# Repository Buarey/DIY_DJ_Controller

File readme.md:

# DIY DJ Controller

Homemade CDJ-style DJ controller with a 3D-printed enclosure, hand-built electronics, and custom firmware.

This repository documents:
- the current stable Mixxx prototype
- the firmware and Mixxx mapping that make it work
- the next hardware direction for a cleaner v2 build
- open-source hardware, firmware, and documentation for builders who want to contribute

<table>
  <tr>
    <td></td>
    <td></td>
  </tr>
  <tr>
    <td></td>
    <td></td>
  </tr>
</table>

## Status

- `v1` is the stable Mixxx-focused version
- the controller has been built, flashed, and used successfully as a working prototype
- Rekordbox was tested, but the jog wheels never became usable enough for a real workflow
- because of that, Rekordbox is not a supported target for this hardware revision

## Current Version

- `MCU`: SparkFun Pro Micro / ATmega32U4
- `Firmware`: PlatformIO + Arduino + `MIDIUSB`
- `Inputs`: `PCF8575` for buttons, `74HC4067` for analog controls, 3 rotary encoders
- `Mechanical`: custom 3D-printed enclosure designed in Fusion 360
- `Software target`: Mixxx

The current prototype includes:
- two-deck transport and loop control
- EQ, filter, gain, volume, tempo, and crossfader control
- jog wheels
- music browsing and load controls

## V1 Hardware Summary

- `MCU`: SparkFun Pro Micro / ATmega32U4
- `Button expander`: `PCF8575` for 16 buttons
- `Analog mux`: `74HC4067` for 15 potentiometers
- `Encoders`: 3 total
  - 1 browse encoder
  - 2 jog wheel encoders
- `Encoder model`: Alps `EC11E` vertical rotary encoder, `H20mm`
- `Button model`: Omron `B3F-40xx`, 12x12 mm THT tactile switch
- `Direct buttons on MCU`: `A1`, `A2`, `A3`
- `Potentiometers`: 15 total
  - `Linear model`: `B103` 75 mm linear slide potentiometer, 10 kOhm
  - `Rotary model`: TT Electronics `P0915N` vertical rotary potentiometer

## V1 Materials List

This is the practical parts list for rebuilding the current working v1 prototype.

| Qty | Material | Notes |
| --- | --- | --- |
| 1 | SparkFun Pro Micro / ATmega32U4 board | The KiCad v1 schematic uses a USB-C Pro Micro clone footprint. Use the matching USB cable for the board you build with. |
| 1 | `PCF8575` / HW-331 16-bit I2C IO expander module | Handles the 16 deck buttons. |
| 1 | `CD74HC4067` / `74HC4067` 16-channel analog multiplexer module | Handles the 15 analog controls. |
| 18 | Omron `B3F-40xx` 12x12 mm THT tactile switches | 16 deck buttons plus 2 direct music-selection buttons. |
| 3 | Alps `EC11E` vertical rotary encoders, `H20mm` | 1 browse encoder plus 2 jog wheel encoders. |
| 10 | TT Electronics `P0915N` vertical rotary potentiometers | Gain, EQ, filter, and other rotary controls. |
| 5 | `B103` 75 mm linear slide potentiometers, 10 kOhm | Deck volume, tempo, and crossfader controls. |
| 1 | 3D-printed enclosure body | `3D models/DIY_CDJ_body.stl`. |
| 1 | 3D-printed enclosure lid | `3D models/DIY_CDJ_lid.stl`. |
| 1 each | 3D-printed caps and control parts | `crossfader.stl`, `cue.stl`, `encoder.stl`, `joggingWheel.stl`, `knob.stl`, `performance-pad.stl`, and `play-pause.stl`. |
| As needed | Hookup wire, solder, and 2.54 mm headers | The stable v1 prototype is hand-wired, not PCB-based. |

The firmware currently defines 3 direct music-selection inputs on `A1`, `A2`, and `A3`, but the KiCad v1 schematic places 18 tactile switches total. Add one extra switch if you wire all 3 direct inputs. The schematic also contains 16 resistor placeholders with no values or footprints assigned yet, so treat those as schematic TODOs rather than an order-ready BOM line.

## V1 Wiring Summary

These are the important firmware-defined connections for the current working Mixxx version.

### Wiring Diagrams

### I2C / Button Expander

- `SDA` -> pin `2`
- `SCL` -> pin `3`
- `PCF8575` address is auto-detected on boot in the `0x20` to `0x27` range

### 74HC4067 Multiplexer

- `MUX signal` -> `A0`
- `S0` -> pin `15`
- `S1` -> pin `14`
- `S2` -> pin `16`
- `S3` -> pin `10`

### Rotary Encoders

- `Browse encoder` -> pins `4` and `5`
- `Jog wheel 1` -> pins `8` and `9`
- `Jog wheel 2` -> pins `6` and `7`

### Direct Buttons

- `A3` -> note `76`
- `A2` -> note `77`
- `A1` -> note `78`

## V1 Current Input Map

### PCF8575 Buttons

- `Button 0` -> Deck 1 Loop Out
- `Button 1` -> Deck 1 Loop In
- `Button 2` -> Deck 1 Hotcue 3
- `Button 3` -> Deck 1 Hotcue 4
- `Button 4` -> Deck 1 Hotcue 1
- `Button 5` -> Deck 1 Hotcue 2
- `Button 6` -> Deck 1 Cue
- `Button 7` -> Deck 1 Play/Pause
- `Button 8` -> Deck 2 Hotcue 4
- `Button 9` -> Deck 2 Hotcue 3
- `Button 10` -> Deck 2 Hotcue 1
- `Button 11` -> Deck 2 Hotcue 2
- `Button 12` -> Deck 2 Cue
- `Button 13` -> Deck 2 Play/Pause
- `Button 14` -> Deck 2 Loop In
- `Button 15` -> Deck 2 Loop Out

### Potentiometers

- `Pot 0 / CC 10` -> Deck 1 Gain
- `Pot 1 / CC 11` -> Deck 2 Gain
- `Pot 2 / CC 12` -> Deck 1 High EQ
- `Pot 3 / CC 13` -> Deck 2 High EQ
- `Pot 4 / CC 14` -> Deck 1 Mid EQ
- `Pot 5 / CC 15` -> Deck 2 Mid EQ
- `Pot 6 / CC 16` -> Deck 1 Low EQ
- `Pot 7 / CC 17` -> Deck 2 Low EQ
- `Pot 8 / CC 18` -> Deck 1 Filter
- `Pot 9 / CC 19` -> Deck 2 Filter
- `Pot 10 / CC 20` -> Deck 2 Volume
- `Pot 11 / CC 21` -> Deck 2 Tempo
- `Pot 12 / CC 22` -> Deck 1 Volume
- `Pot 13 / CC 23` -> Crossfader
- `Pot 14 / CC 24` -> Deck 1 Tempo

### Browser And Jog Controls

- `Browse encoder / CC 25` -> library scroll
- `A1 / note 78` -> Load selected track to Deck 1
- `A2 / note 77` -> Load selected track to Deck 2
- `A3 / note 76` -> Enter or expand selected folder
- `Jog wheel on pins 8/9 / CC 26` -> currently mapped to Deck 2
- `Jog wheel on pins 6/7 / CC 27` -> currently mapped to Deck 1

## V1 Firmware

The current firmware lives in `CDJ_firmware/src/main.cpp`.

### Current Behavior

- auto-detects the `PCF8575` on boot
- configures the expander pins as input pull-high
- reads 16 buttons through the `PCF8575`
- reads 15 analog controls through the `74HC4067`
- reads 3 rotary encoders
- reads direct top buttons on `A1`, `A2`, and `A3`
- sends MIDI note and CC messages through `MIDIUSB`
- uses an additional filter on the browse encoder to reduce event spam in Mixxx

### Build Target

`CDJ_firmware/platformio.ini` currently targets:

```ini
[env:sparkfun_promicro16]
platform = atmelavr
board = sparkfun_promicro16
framework = arduino
lib_deps =
  arduino-libraries/MIDIUSB @ ^1.0.5
```

## Repo Layout

- `CDJ_firmware/` - firmware source and PlatformIO config
- `controllers/mixx_Mapping/` - Mixxx XML and JS mapping
- `controllers/rekordbox/` - Rekordbox mapping reference and notes
- `pics/` - renders and prototype photos
- `reference circuits/` - circuit reference images
- `PCB/` - KiCad schematic, PCB, and custom symbols/footprints
- `3D models/` - printable parts and Fusion 360 source archive
- `CONTRIBUTING.md` - contribution guide
- `.github/` - issue templates, pull request template, and CI workflow

## Source Of Truth

- `Firmware`: `CDJ_firmware/src/main.cpp`
- `Mixxx XML mapping`: `controllers/mixx_Mapping/DJC-DIY.midi.xml`
- `Mixxx JS mapping`: `controllers/mixx_Mapping/DJC-DIY-scripts.js`

For exact control behavior, use those files instead of this README.

## Contributing

Contributions are welcome. The most useful contributions right now are practical build reports, Mixxx mapping fixes, firmware cleanup, PCB review, parts substitutions, enclosure fit notes, and documentation improvements.

Before starting a large hardware or firmware change, open an issue so the direction can be discussed. Small documentation fixes can go straight to a pull request.

Useful starter work:

- test the current Mixxx mapping on another OS or Mixxx version
- document compatible Pro Micro clones, encoders, buttons, and potentiometers
- improve wiring photos or assembly notes
- review the KiCad v1 schematic and PCB TODOs
- add real build notes for 3D-print settings and fit adjustments

See `CONTRIBUTING.md` for the full workflow and pull request checklist.

## Getting Started

### Firmware

1. Install [PlatformIO](https://platformio.org/) in VS Code.
2. Open `CDJ_firmware/`.
3. Connect the SparkFun Pro Micro by USB.
4. Build or upload:

```bash
pio run
pio run --target upload
```

### Mixxx

Copy these files into your Mixxx controller mapping folder:

- `controllers/mixx_Mapping/DJC-DIY.midi.xml`
- `controllers/mixx_Mapping/DJC-DIY-scripts.js`

Then enable the mapping in Mixxx.

## Important Notes

- The stable path for this project is Mixxx, not Rekordbox.
- The prototype is still hand-wired and not PCB-based yet.
- The current jog wheel assignment is swapped between physical control and deck mapping.
- Rekordbox support should be treated as future hardware research, not a feature of this version.

## V2 Plan

V2 is a hardware redesign focused on one goal: keep a single `USB-C` cable to the computer and add a built-in `3.5 mm` headphone cue output.

- `Master` stays on the computer side
- the controller provides only `Headphones / Cue`
- the project stays Mixxx-first

### Electronics Plan

- `Prototype MCU`: `SparkFun Thing Plus ESP32-S3`
- `Custom PCB MCU`: `ESP32-S3-WROOM-1`
- `Headphone audio`: `Adafruit TLV320DAC3100` or equivalent small I2S headphone DAC/codec
- `External ports`: one `USB-C`, one `3.5 mm TRS` headphone jack
- `Existing controls to keep initially`: `PCF8575`, `74HC4067`, jog encoders, browse encoder, buttons, and potentiometers

### Core Connections

- `USB-C` -> `ESP32-S3`
- `ESP32-S3 I2S` -> `TLV320DAC3100` audio data
- `ESP32-S3 I2C` -> `TLV320DAC3100` configuration
- `TLV320DAC3100` -> `3.5 mm TRS` headphone jack
- `ESP32-S3` -> existing control hardware

### Firmware Work

- port the controller logic from `ATmega32U4` to `ESP32-S3`
- expose one composite USB device with `MIDI + audio`
- keep the current control behavior as close to `v1` as possible
- send Mixxx cue audio to the headphone DAC

### Rekordbox Note

`ESP32-S3` is a much better platform for future USB experiments, but it does not guarantee Rekordbox compatibility or working jog wheels. V2 should still be treated as a Mixxx-first design.

## License

This project uses separate licenses by file type:

| Files | License |
| --- | --- |
| Firmware and controller mappings | GNU General Public License v3.0 only (`GPL-3.0-only`) |
| PCB, wiring, CAD, and 3D hardware design files | CERN Open Hardware Licence Version 2 - Strongly Reciprocal (`CERN-OHL-S-2.0`) |
| Documentation, photos, videos, and other media | Creative Commons Attribution 4.0 International (`CC-BY-4.0`) |

See `LICENSE.md`, `LICENSE-SOFTWARE.txt`, `LICENSE-HARDWARE.txt`, and `LICENSE-DOCS.txt` for details.

This project was inspired by my friend [@mandiclab](https://github.com/mandiclab) and the [djc-diy](https://github.com/mandiclab/djc-diy) project.

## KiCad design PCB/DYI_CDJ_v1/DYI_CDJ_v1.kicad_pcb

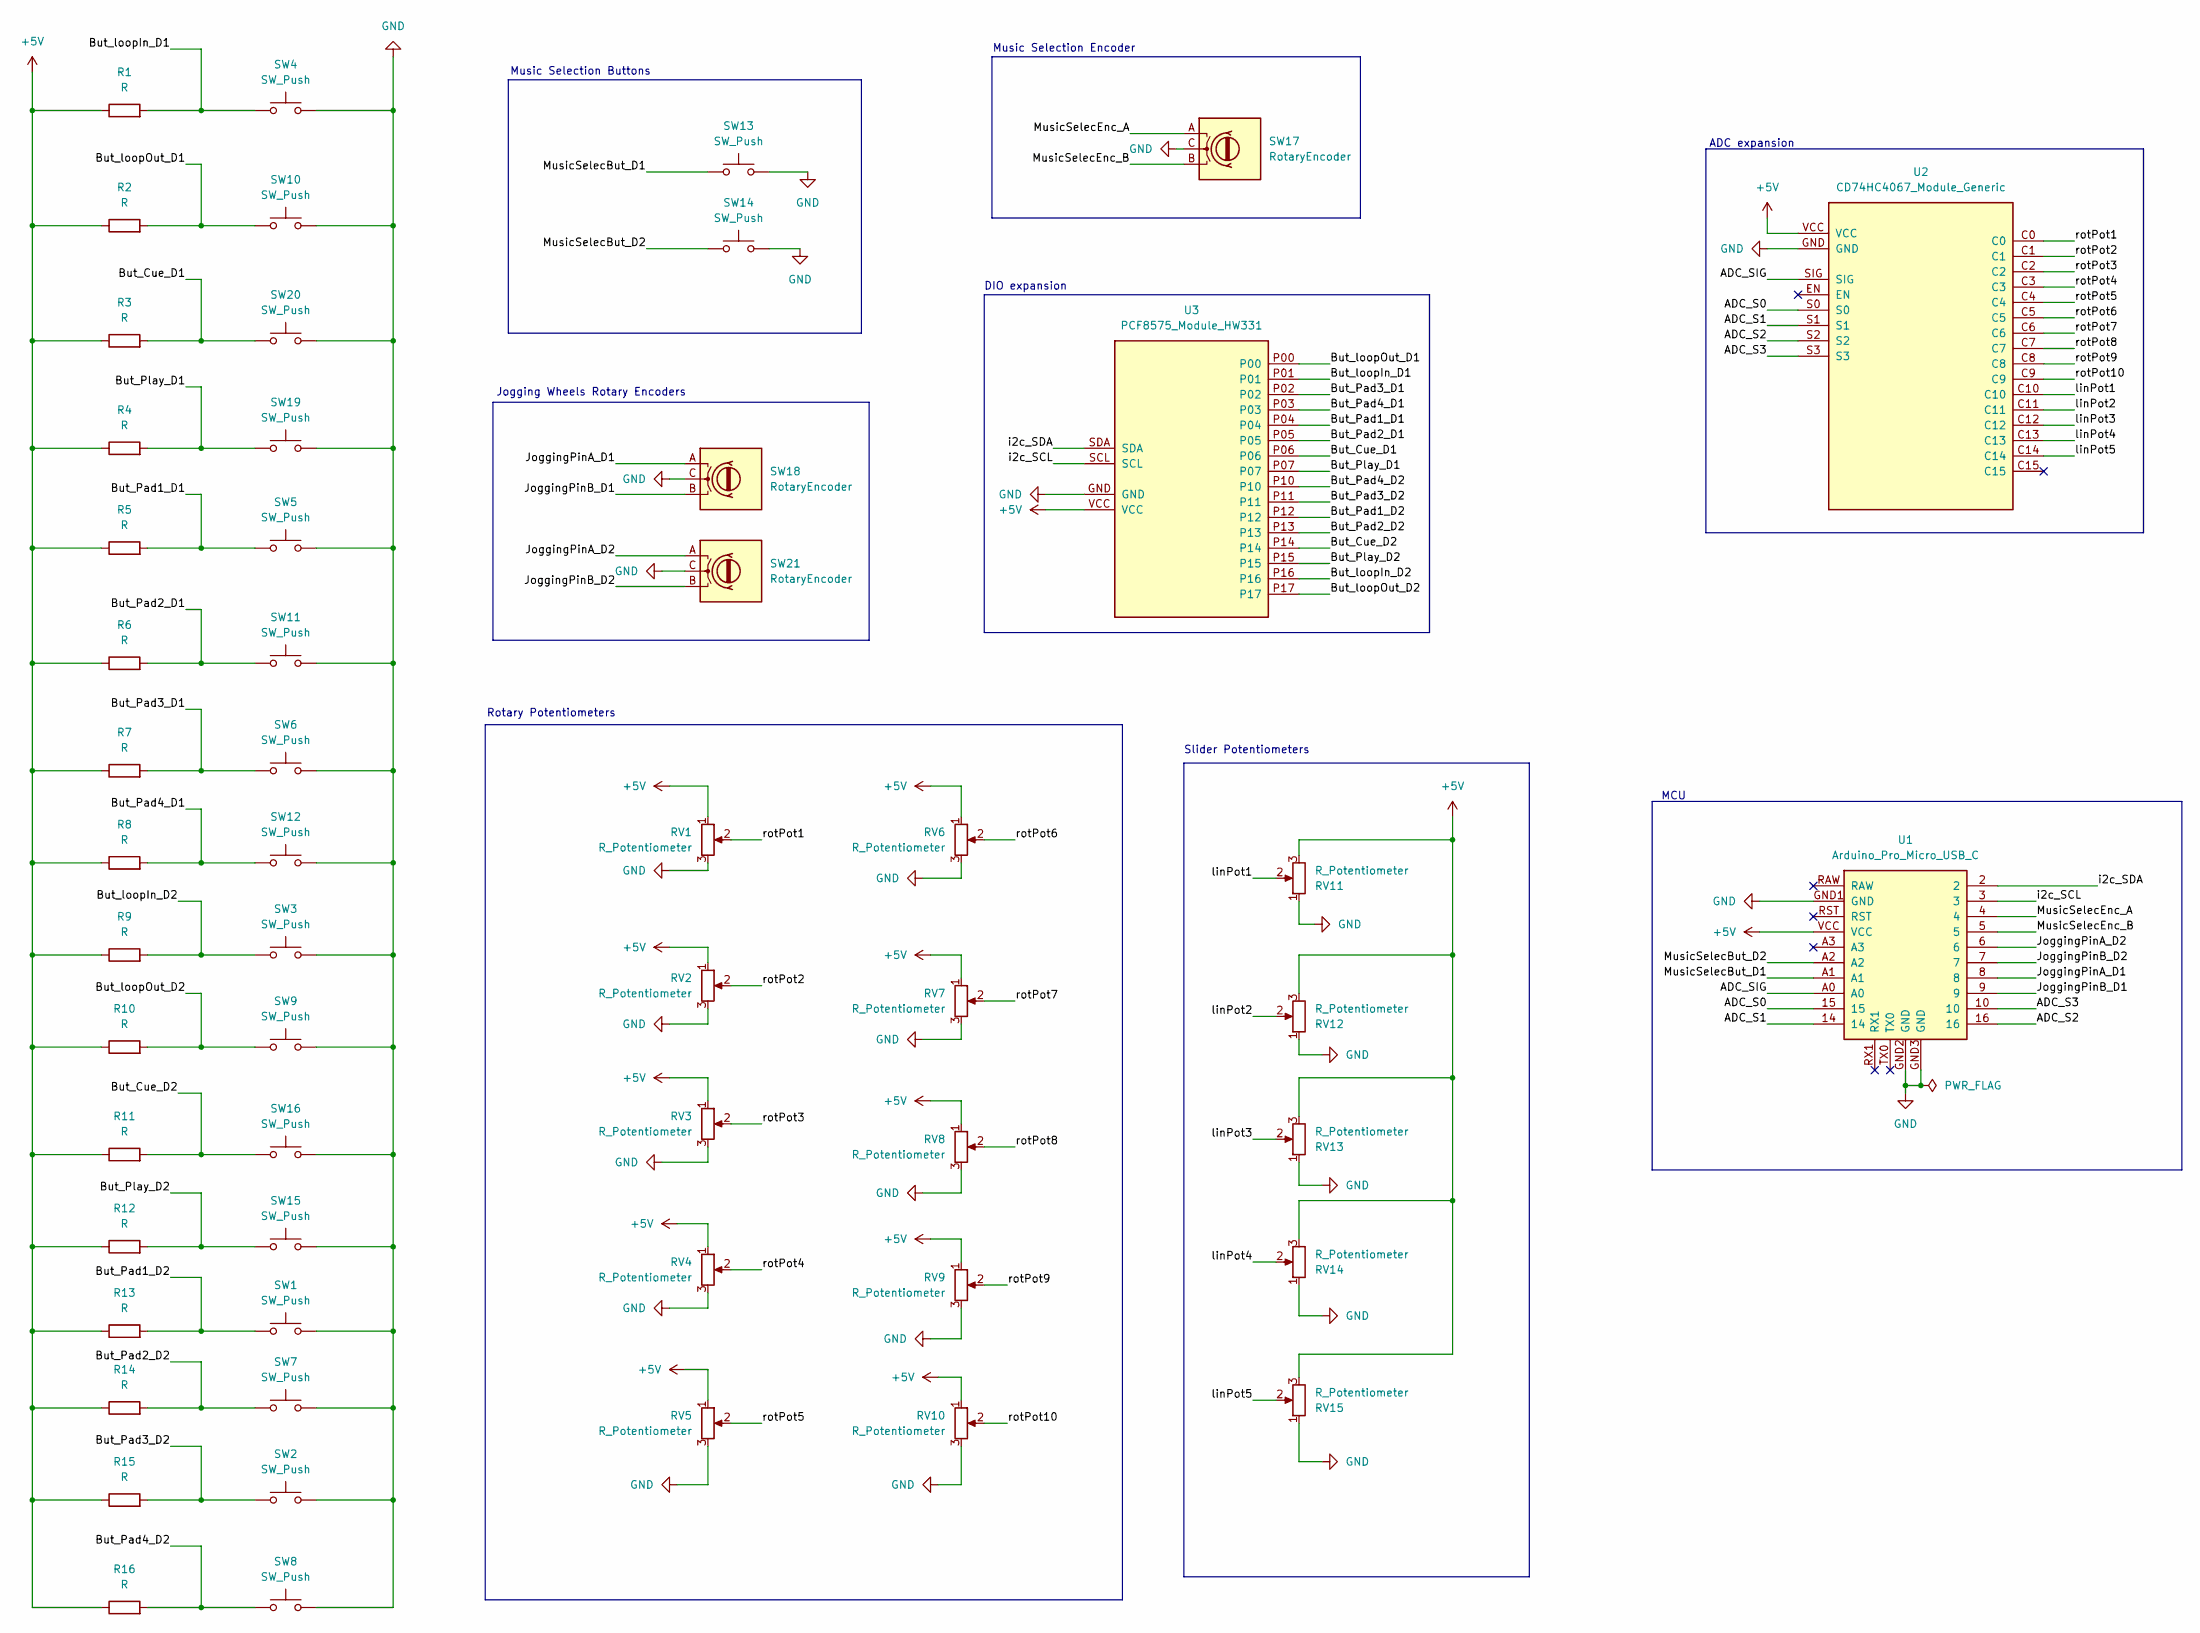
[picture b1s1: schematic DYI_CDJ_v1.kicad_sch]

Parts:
R1, R2, R3, R4, R5, R6, R7, R8, R9, R10, R11, R12, R13, R14, R15, R16: R; R_Axial_DIN0207_L6.3mm_D2.5mm_P10.16mm_Horizontal
RV1, RV2, RV3, RV4, RV5, RV6, RV7, RV8, RV9, RV10: R_Potentiometer; Potentiometer_TT_P0915N
RV11, RV12, RV13, RV14, RV15: R_Potentiometer; Potentiometer_Bourns_PTA6043_Single_Slide
SW1, SW2, SW3, SW4, SW5, SW6, SW7, SW8, SW9, SW10, SW11, SW12, SW13, SW14, SW15, SW16, SW19, SW20: SW_Push; SW_SPST_Omron_B3F-40xx
SW17, SW18, SW21: RotaryEncoder; RotaryEncoder_Alps_EC11E_Vertical_H20mm
U1: Arduino_Pro_Micro_USB_C; Arduino_Pro_Micro_USB_C_36.8x17.7mm
U2: CD74HC4067_Module_Generic
U3: PCF8575_Module_HW331

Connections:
+5V: R1.1, R2.1, R3.1, R4.1, R5.1, R6.1, R7.1, R8.1, R9.1, R10.1, R11.1, R12.1, R13.1, R14.1, R15.1, R16.1, RV1.1, RV2.1, RV3.1, RV4.1, RV5.1, RV6.1, RV7.1, RV8.1, RV9.1, RV10.1, RV11.3, RV12.3, RV13.3, RV14.3, RV15.3, U1.VCC, U2.VCC, U3.VCC
/ADC_S0: U1.15, U2.S0
/ADC_S1: U1.14, U2.S1
/ADC_S2: U1.16, U2.S2
/ADC_S3: U1.10, U2.S3
/ADC_SIG: U1.A0, U2.SIG
/But_Cue_D1: R3.2, SW20.1, U3.P06
/But_Cue_D2: R11.2, SW16.1, U3.P14
/But_Pad1_D1: R5.2, SW5.1, U3.P04
/But_Pad1_D2: R13.2, SW1.1, U3.P12
/But_Pad2_D1: R6.2, SW11.1, U3.P05
/But_Pad2_D2: R14.2, SW7.1, U3.P13
/But_Pad3_D1: R7.2, SW6.1, U3.P02
/But_Pad3_D2: R15.2, SW2.1, U3.P11
/But_Pad4_D1: R8.2, SW12.1, U3.P03
/But_Pad4_D2: R16.2, SW8.1, U3.P10
/But_Play_D1: R4.2, SW19.1, U3.P07
/But_Play_D2: R12.2, SW15.1, U3.P15
/But_loopIn_D1: R1.2, SW4.1, U3.P01
/But_loopIn_D2: R9.2, SW3.1, U3.P16
/But_loopOut_D1: R2.2, SW10.1, U3.P00
/But_loopOut_D2: R10.2, SW9.1, U3.P17
/JoggingPinA_D1: SW18.A, U1.8
/JoggingPinA_D2: SW21.A, U1.6
/JoggingPinB_D1: SW18.B, U1.9
/JoggingPinB_D2: SW21.B, U1.7
/MusicSelecBut_D1: SW13.1, U1.A1
/MusicSelecBut_D2: SW14.1, U1.A2
/MusicSelecEnc_A: SW17.A, U1.4
/MusicSelecEnc_B: SW17.B, U1.5
/i2c_SCL: U1.3, U3.SCL
/i2c_SDA: U1.2, U3.SDA
/linPot1: RV11.2, U2.C10
/linPot2: RV12.2, U2.C11
/linPot3: RV13.2, U2.C12
/linPot4: RV14.2, U2.C13
/linPot5: RV15.2, U2.C14
/rotPot1: RV1.2, U2.C0
/rotPot2: RV2.2, U2.C1
/rotPot3: RV3.2, U2.C2
/rotPot4: RV4.2, U2.C3
/rotPot5: RV5.2, U2.C4
/rotPot6: RV6.2, U2.C5
/rotPot7: RV7.2, U2.C6
/rotPot8: RV8.2, U2.C7
/rotPot9: RV9.2, U2.C8
/rotPot10: RV10.2, U2.C9
GND: RV1.3, RV2.3, RV3.3, RV4.3, RV5.3, RV6.3, RV7.3, RV8.3, RV9.3, RV10.3, RV11.1, RV12.1, RV13.1, RV14.1, RV15.1, SW1.2, SW2.2, SW3.2, SW4.2, SW5.2, SW6.2, SW7.2, SW8.2, SW9.2, SW10.2, SW11.2, SW12.2, SW13.2, SW14.2, SW15.2, SW16.2, SW17.C, SW18.C, SW19.2, SW20.2, SW21.C, U1.GND1 (GND), U1.GND2 (GND), U1.GND3 (GND), U2.GND, U3.GND

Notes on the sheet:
Music Selection Buttons
Music Selection Encoder
DIO expansion
Jogging Wheels Rotary Encoders
Slider Potentiometers
ADC expansion
Rotary Potentiometers
MCU

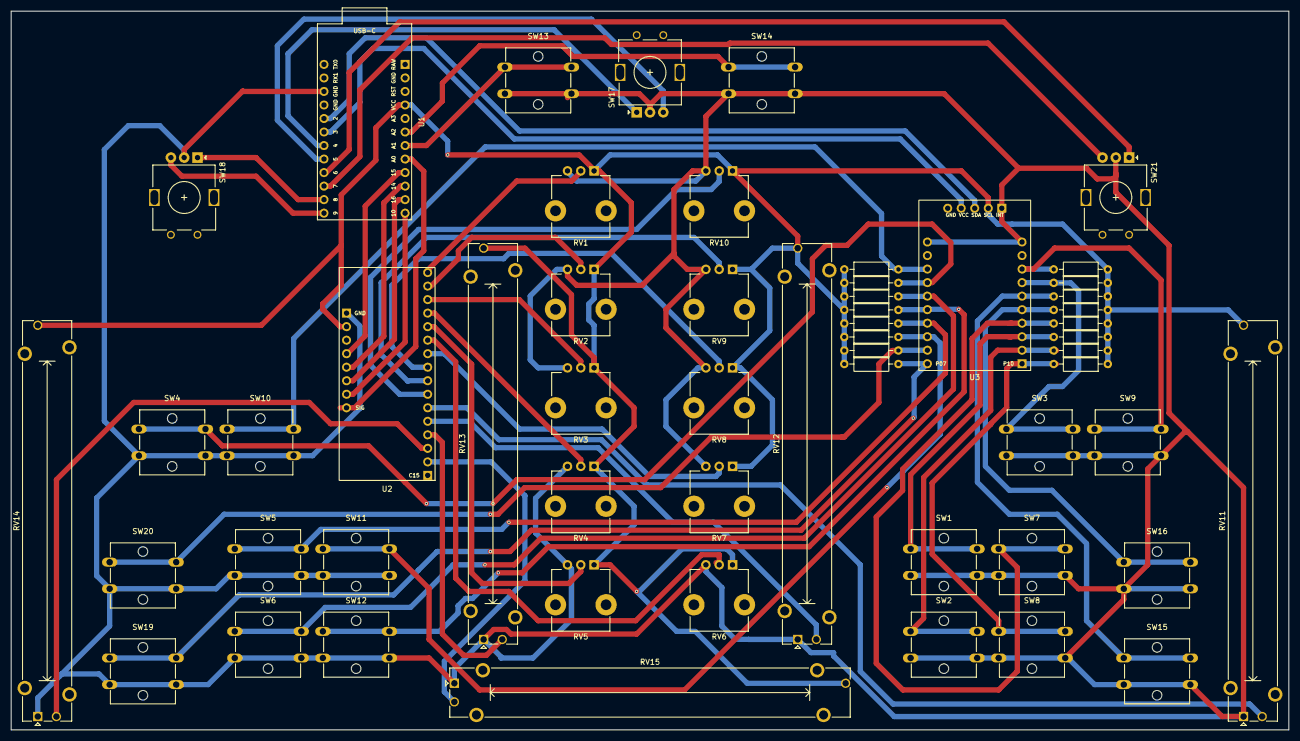
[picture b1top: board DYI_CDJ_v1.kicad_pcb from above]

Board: 2 copper layers, 240.0 x 135.0 mm, 55 parts (0 on the bottom side), 48 nets.

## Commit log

2026-05-10 Add v1 materials list to README
2026-05-10 Remove tracked .DS_Store files
2026-05-10 Correct v1 button materials count
2026-06-02 developing PCB
2026-06-04 Prepare project for open-source contributions
2026-06-04 Bump actions/checkout from 4 to 6
    Bumps [actions/checkout](https://github.com/actions/checkout) from 4 to 6.
    - [Release notes](https://github.com/actions/checkout/releases)
    - [Changelog](https://github.com/actions/checkout/blob/main/CHANGELOG.md)
    - [Commits](https://github.com/actions/checkout/compare/v4...v6)
    ---
    updated-dependencies:
2026-06-05 Bump actions/setup-python from 5 to 6
    Bumps [actions/setup-python](https://github.com/actions/setup-python) from 5 to 6.
    - [Release notes](https://github.com/actions/setup-python/releases)
    - [Commits](https://github.com/actions/setup-python/compare/v5...v6)
    ---
    updated-dependencies:
    - dependency-name: actions/setup-python
2026-06-11 Update README photos
2026-06-25 PCB update dev
2026-06-25 Models and modifed source code
    Added missig 3D models + alternatives
    Added alternative Mixxx mapping
    Replaced original source code with modified one (tact buttons didn't work after reboot)
